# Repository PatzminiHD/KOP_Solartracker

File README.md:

# Solartracker

Here we design the idea for one of our school projects, a solartracker.
This repository is now archived as the project is finished.
The presentation can be found [here](https://github.com/PatzminiHD/KOP_Solartracker/tree/main/Presentation), and the video [here](https://youtu.be/DB9Xd0maCpQ).

### Given Requirements:
- It should have 2 axes to follow the position of the sun
- Design a mechanical concept to turn and tilt a solar cell and make a 3D CAD Model of the concept
- The tracker should be controlled by an Arduino
- Document the Code in a program flow chart

### Provided Materials:
- 1x [Solarcell](https://www.conrad.at/de/p/sol-expert-sm2380-sm2380-solarmodul-190469.html "Link")
- 2x [Servo](https://www.conrad.at/de/p/reely-midi-servo-analog-servo-getriebe-material-plastik-stecksystem-jr-2144550.html?searchType=SearchRedirect "Link")
- 4x [Light Depending Resistor](https://www.conrad.at/de/p/luna-optoelectronics-pdv-p8103-fotowiderstand-ldr-tht-1-st-150-v-max-l-x-b-x-h-4-29-x-5-08-x-2-mm-1762910.html?searchType=SearchRedirect "Link")

### TODO
- ~~Add Imbuss-Wormscrew to asm~~
- ~~Arduino Program turn 180° on Servo max Value~~
- ~~Debug Arduino Program (correct Movement based on LDRs)~~
- Smooth movement when controlling with Poti
- ~~Add Setup Text on Display~~
- ~~HTL Logo on Program Setup(?)~~
- ~~List Ideas for Video Script~~
- ~~Add Logos~~
- ~~Add Poti~~
- ~~Imbuss-Wormscrew for Locking Ring~~
- ~~Mounting points for Cables~~
- ~~Add Side Box Attachments~~
- ~~Servo Attachment in Bottom Box~~
- ~~Assembley all Screws~~
- ~~Rethink positioning of LDRs~~
- ~~Draw locking ring for Main Axle~~
- ~~Draw Case removeable Wall~~
- ~~Add Audio Port to the Case~~
- ~~Bottom Box rethink/remake~~
- ~~Add LED to PSU~~
- ~~Add Walls to LDR Mount~~

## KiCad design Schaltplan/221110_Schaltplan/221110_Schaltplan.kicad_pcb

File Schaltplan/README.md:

# Curcuit Diagram

This directory contains the Curcuit diagram made using [KiCad](https://www.kicad.org/).

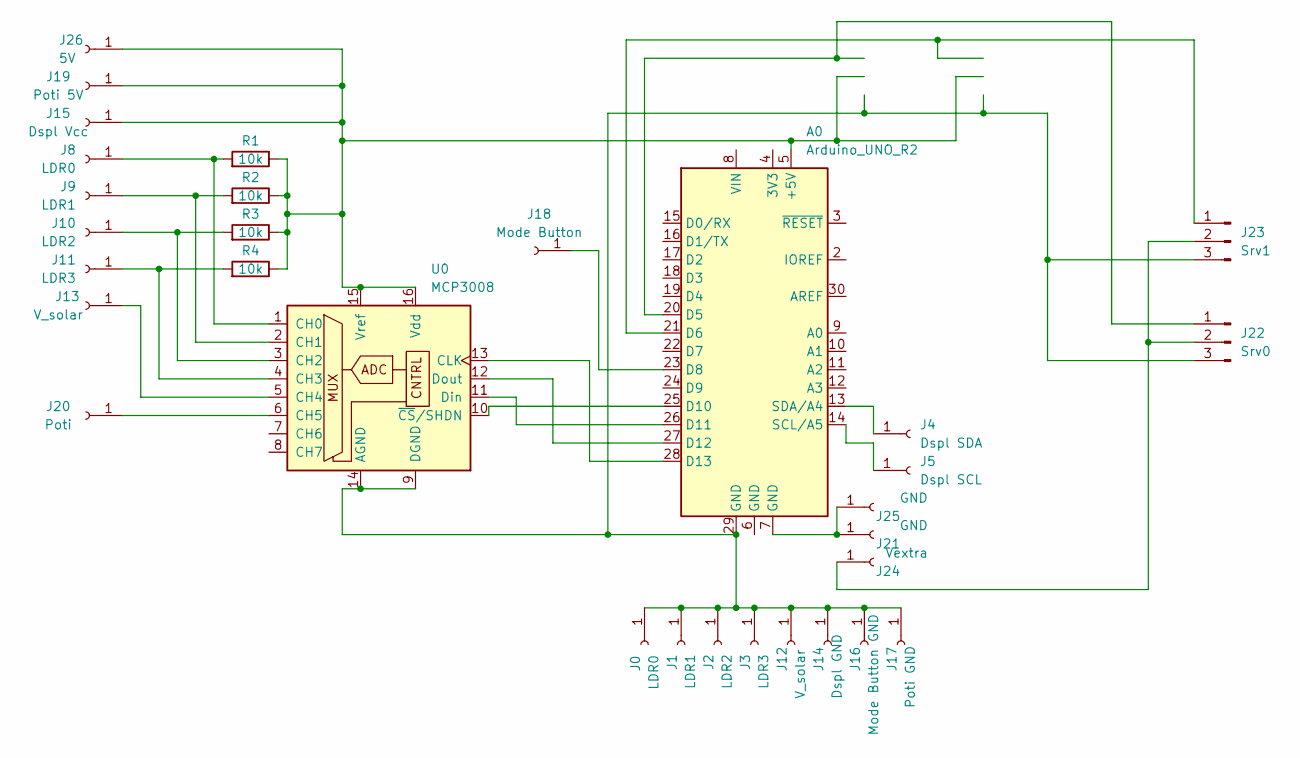
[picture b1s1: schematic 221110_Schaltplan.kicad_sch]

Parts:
A0: Arduino_UNO_R2
J0, J8: LDR0; PinHeader_1x01_P2.54mm_Vertical
J1, J9: LDR1; PinHeader_1x01_P2.54mm_Vertical
J2, J10: LDR2; PinHeader_1x01_P2.54mm_Vertical
J3, J11: LDR3; PinHeader_1x01_P2.54mm_Vertical
J4: Dspl SDA; PinHeader_1x01_P2.54mm_Vertical
J5: Dspl SCL; PinHeader_1x01_P2.54mm_Vertical
J12, J13: V_solar; PinHeader_1x01_P2.54mm_Vertical
J14: Dspl GND; PinHeader_1x01_P2.54mm_Vertical
J15: Dspl Vcc; PinHeader_1x01_P2.54mm_Vertical
J16: Mode Button GND; PinHeader_1x01_P2.54mm_Vertical
J17: Poti GND; PinHeader_1x01_P2.54mm_Vertical
J18: Mode Button; PinHeader_1x01_P2.54mm_Vertical
J19: Poti 5V; PinHeader_1x01_P2.54mm_Vertical
J20: Poti; PinHeader_1x01_P2.54mm_Vertical
J21, J25: GND; PinHeader_1x01_P2.54mm_Vertical
J22: Srv0; PinHeader_1x03_P2.54mm_Vertical
J23: Srv1; PinHeader_1x03_P2.54mm_Vertical
J24: Vextra; PinHeader_1x01_P2.54mm_Vertical
J26: 5V; PinHeader_1x01_P2.54mm_Vertical
R1, R2, R3, R4: 10k; R_Axial_DIN0207_L6.3mm_D2.5mm_P10.16mm_Horizontal
U0: MCP3008; DIP-16_W7.62mm_Socket

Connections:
unnamed: A0.5 (+5V), J15.1, J19.1, J26.1, R1.1, R2.1, R3.1, R4.1, U0.15 (Vref), U0.16 (Vdd)
unnamed: A0.13 (SDA/A4), J4.1
unnamed: A0.14 (SCL/A5), J5.1
unnamed: A0.20 (D5), J22.1
unnamed: A0.21 (D6), J23.1
unnamed: A0.23 (D8), J18.1
unnamed: A0.25 (D10), U0.10 (~CS/SHDN)
unnamed: A0.26 (D11), U0.11 (Din)
unnamed: A0.27 (D12), U0.12 (Dout)
unnamed: A0.28 (D13), U0.13 (CLK)
unnamed: A0.29 (GND), J0.1, J1.1, J2.1, J3.1, J12.1, J14.1, J16.1, J17.1, J22.3, J23.3, U0.9 (DGND), U0.14 (AGND)
unnamed: J8.1, R1.2, U0.1 (CH0)
unnamed: J9.1, R2.2, U0.2 (CH1)
unnamed: J10.1, R3.2, U0.3 (CH2)
unnamed: J11.1, R4.2, U0.4 (CH3)
unnamed: J13.1, U0.5 (CH4)
unnamed: J20.1, U0.6 (CH5)
unnamed: A0.7 (GND), J21.1, J25.1
unnamed: J22.2, J23.2, J24.1

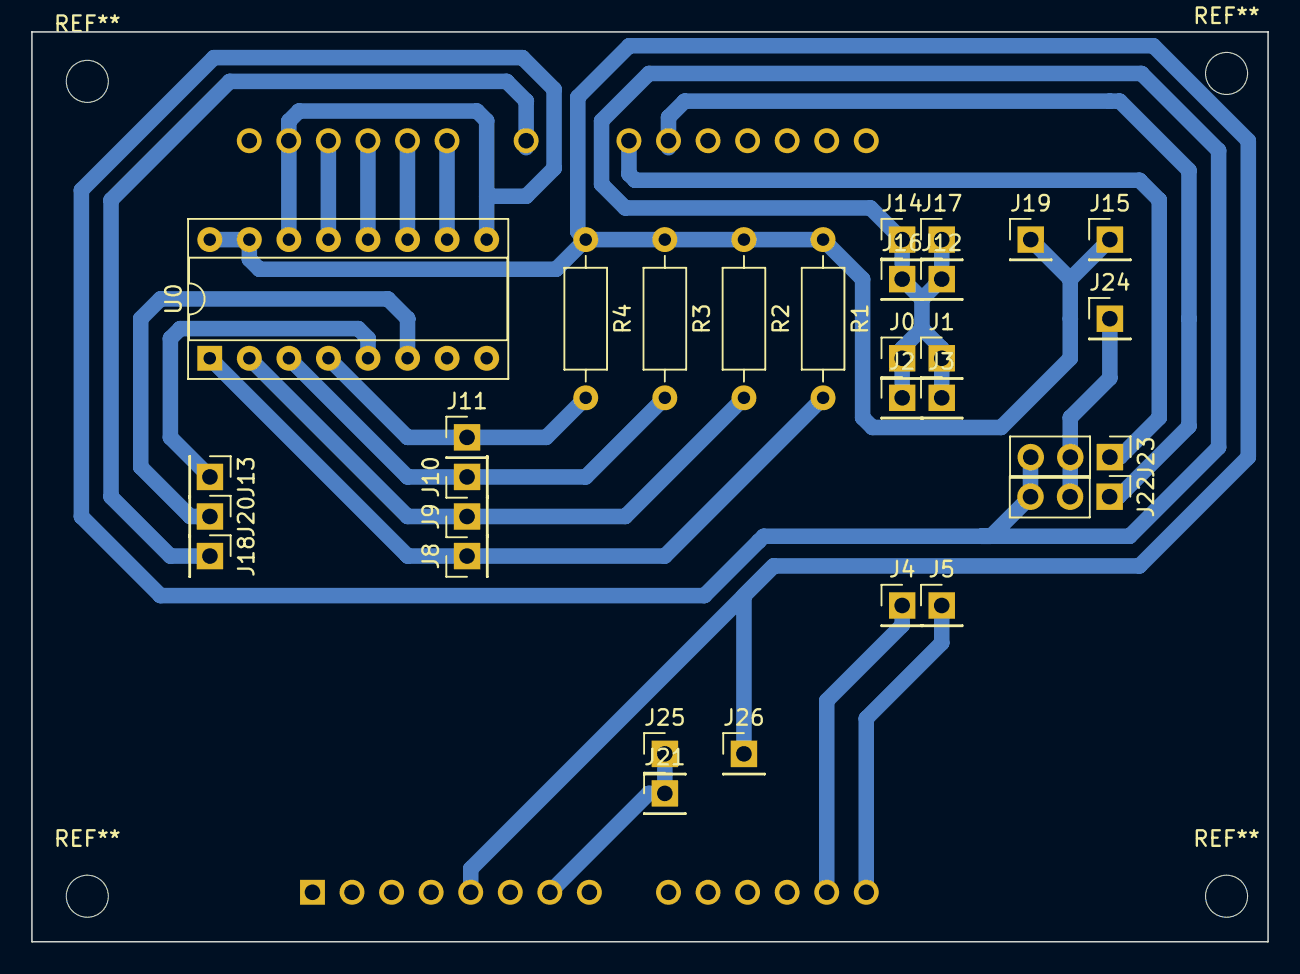
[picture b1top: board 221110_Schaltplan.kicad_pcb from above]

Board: 2 copper layers, 79.4 x 58.4 mm, 31 parts (1 on the bottom side), 19 nets.

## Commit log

2022-11-03 Add 3D Model of solar cell, start construction of Solarcell Holder
2022-11-04 Test Things
2022-11-05 Add Assembly
2022-11-05 test
2022-11-05 Commit Test 1
2022-11-05 Add Raspi 3D Model
2022-11-05 Add Kugellager Dimensionen
2022-11-05 add Arduino 3dFile
2022-11-05 Export Arduuno.asm from STEP
2022-11-06 add Bottom-box and asm_all
2022-11-06 Work on Solarcell Holder
2022-11-06 Add Antrieb Konzept
2022-11-06 fix_Arduinobefestigung
2022-11-06 Add Gears
2022-11-07 Add 3D Model of Servo Attachment for Large Gear
2022-11-07 Cut Gear Attachment from Gear
2022-11-10 Konzept
2022-11-10 Arduinobefestigung_Fix
2022-11-10 Add KiCad Project for Schaltplan
2022-11-10 Wichtige_Änderungen
2022-11-10 Work on Schaltplan
2022-11-12 Add README.md
2022-11-12 Write Readme
2022-11-13 Move CAD Files and Concepts to Subdirectory
2022-11-17 Test Commits
2022-11-17 Add ADC to Curcuit Diagram
2022-11-19 top plate/lcd support
2022-11-19 Assemble all parts. Add needed parts. Fix parts
2022-11-23 Add missing Connector; Fix Name of Connector
2022-11-24 Add Program Flow Chart
2022-11-24 Kop fix
2022-12-01 Add Arduino_Program
2022-12-01 Add PNGs for Custom Characters
2022-12-01 Add Pin numbers
2022-12-01 Add CustomChars and Setup
2022-12-01 Add Code to change Mode
2022-12-01 Case_Remake
2022-12-01 Add Method to write current Mode to LCD
2022-12-02 Add Connector for Mode Button and Poti
2022-12-02 Add Footprints to Schematic
2022-12-02 Add PCB
2022-12-03 Add PinNumber for Pins on ADC
2022-12-03 Add Method to read from ADC
2022-12-03 Add Methods for every Mode
2022-12-15 Add Auto Mode
2022-12-15 Add Comments
2022-12-15 Finish Schaltplan
2022-12-15 Change CircuitDiagram to match new CAD Design
2022-12-18 Add 1st PSU
2022-12-18 Add 2nd PSU
2022-12-18 add psu case
2022-12-18 Work on PSUs
2022-12-19 Fix position of PSU_A2
2022-12-22 add psu_top
2022-12-22 Add AUX Port
2022-12-22 add psu fix
2022-12-23 Add Countersunk Screws
2022-12-23 Add Phillips Head
2022-12-23 add psu cuntersunk+lever hole
2022-12-23 add fix
2022-12-23 Add Switch
2023-01-06 Make hole for AUX Port smaller
2023-01-06 Add Holes for power wires
2023-01-06 Add Switch and AUX Port to asm
2023-01-06 Add Cables and Harness
2023-01-06 Add Cables between PSUs and Switch
2023-01-12 Add Label to Case
2023-01-12 Add TODOs to Readme
2023-01-12 Add LED Holes to PSU Case
2023-01-12 add case_remake
2023-01-12 add case fix
2023-01-12 Add LED
2023-01-14 case delete files
2023-01-14 Make PSU Case ready for 3D Printing
2023-01-14 Add Debug Statements
2023-01-14 add case holes and assemble bearings
2023-01-14 add random section
2023-01-14 Add Mounting Holes to PCB + Export to STEP
2023-01-14 Export STEP with Components
2023-01-14 add case_display+holder
2023-01-14 Add Assembly with Arduino and PCB
2023-01-15 Add READMEs to Subdirectories
2023-01-15 add case button
2023-01-15 Add LDRs, Finish LEDs with R, Add them to assemblies
2023-01-18 Case_Einzelzusammenbau
2023-01-19 add new Assembly, add new ToDo's
2023-01-19 Add Connecting Rod
2023-01-19 Make Rod Longer
2023-01-19 turn parts 180°
2023-01-19 add connecting rod to Assembly
2023-01-21 Add CAM and GERBER Files
2023-01-21 Add CAM and LMD File
2023-01-26 add case holes for arduino
2023-01-26 Add Pictures of ProgramFlowChart
2023-01-26 add sideplate
2023-01-26 fix asm
2023-01-26 Add Files for Drawing
2023-01-26 add magnets
2023-01-28 Add Drawings
2023-01-28 add aux port to case
2023-01-28 add new case to asm
2023-01-29 add LCD Support drawing
2023-01-29 add servo cable hole
2023-01-29 Add PLA Material
2023-01-29 add Servohalter drawing
2023-01-30 Work on drawings
2023-01-30 change README
2023-01-31 add lower servo Attachment
2023-02-01 Add STL Files for Gears
2023-02-02 add drawing and screws
2023-02-02 drawing solarcell holder
2023-02-02 add screws for servo
2023-02-02 cahnge
2023-02-03 Add Gears version 2 and 3
2023-02-03 Export New Gears as STL Files
2023-02-04 modify servohalter and add stl file
2023-02-04 Add Key Test Part for Top Plate
2023-02-04 Add Gears to Assembly_All
2023-02-05 Add Design Tests
2023-02-05 Update Design Test
2023-02-06 Add Gear Values
2023-02-09 add design
2023-02-09 add HTL Logo to case
2023-02-11 add locking ring holes+stl file
2023-02-11 FIx Servohalter
2023-02-11 Fix Typo
2023-02-11 reassemble servohalter screws
2023-02-11 add lcd servo stl file
2023-02-11 add solarcell_holder stl file
2023-02-12 Fix Servo Size and Orientation
2023-02-12 add bottomplate stl+screw hole fix
2023-02-12 Add Holes to large gear
2023-02-12 add PMMA Platte
2023-02-13 add new lcdsupport_servo stl file
2023-02-13 Enlarge Hole for Screw
2023-02-13 Add Cable Mounting Points
2023-02-13 add mount case_display_holder
2023-02-14 Fix Size of PMMA Plate
2023-02-14 Move hexagons inwards
2023-02-14 change pmma plate+ add casesideplate stl file
2023-02-14 fix location of the magnets and the sideplate
2023-02-15 Create Drawing of PMMA Plate
2023-02-15 Add Basic Shape of Poti
2023-02-15 Add Notch
2023-02-15 add poti to asm + add poti hole to case_display_holder
2023-02-15 add hier könnte ihre werbung stehen
2023-02-15 Make Poti Prettier
2023-02-19 add stl files for case and display holder
2023-02-19 Add G-Code temporarily
2023-02-22 Increase Tolerance of Locking Ring
2023-03-07 add new lcd support stl file
2023-03-09 Drawing Top Plate
2023-03-23 LCDSUPPORT
2023-03-23 lcdsupport drawing
2023-03-23 Top plate drawing
2023-03-29 add pdf drawing
2023-04-01 Add TODOs
2023-04-01 Add TODO
2023-04-03 pdf verschieben
2023-04-03 add Videoscript
2023-04-06 Translate Videoscript to English
2023-04-07 Format english Videoscript as Markdown
2023-04-12 Add Turn logic
2023-04-12 Remove unnecessary if statement
2023-04-12 Improve Memory Usage
2023-04-13 Fine tune constants; fix errors; Remove unnecessary code
2023-04-13 display holder drawing
2023-04-13 Bottomplate Drw
2023-04-14 Fix critical typo
2023-04-14 Remove Debug Statements
2023-04-14 fix bug
2023-04-14 Update Magic Numbers
2023-04-20 Save Custom Chars to program memory
2023-04-20 Save all constans to program memory
2023-04-20 Video Zusammenbau
2023-04-22 Do not save constants to PROGMEM
2023-04-22 Remove unnecessary file
2023-04-27 Rename Videoscript to Video Ideas
2023-04-27 add Video script and Kostenrechnung
2023-05-11 Fix bug in Manual Servo controll
2023-05-11 update cost list
2023-05-11 add new drawing
2023-05-15 Include two games
2023-05-25 pmma plate coloring
2023-05-25 fix drawing
2023-05-25 Aufnahmeliste
2023-05-25 Fix the wrong value read by MCP3008
2023-05-25 update servohalter drawing
2023-05-25 Activate Games when pressing button
2023-05-29 add explosion and asm_drawing
2023-05-29 add Circular Reference
2023-05-29 Work on Assembly Drawing
2023-05-30 Fix moved Baloons
2023-05-30 Add Comments to Arduino Bird
2023-05-30 Add Comments to Arduino Breakout
2023-05-30 work on drawing and materials
2023-06-01 Add List of Components as Excel Table
2023-06-15 add powerpoint
2023-06-20 Add presentation Text
2023-06-20 Work on PPP
2023-06-20 Update TODO
2023-06-20 update Presentation
2023-06-20 QR-Code hinzufügen
2023-06-20 Work on PP Text
2023-06-22 update ppp
2023-07-17 Ultimate Purge
